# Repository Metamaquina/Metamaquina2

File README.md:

Metamaquina2
============

Metamaquina 2 - fully parametric 3D printer

Manufacturing Instructions
==========================

This is a 3d printer project that is completely designed using the parametric CAD tools
 provided by OpenSCAD. In order to deal with this source code you'll need to install OpenSCAD,
following the instructions at: www.openscad.org

The main structure of the machine is built using lasercut MDF panels. The curves for lasercutting 
can be exported to DXF by rendering the lasercutter_6mm_MDF.scad file. Open it in OpenSCAD, press F6 (to compile) and then click Design->Export DXF. The resulting DXF file can be used to cut 6mm thick MDF sheets (or you can change the thickness in the source if you plan to work with some other materials but be sure to review the 3d model in this case since some parts of the design depend on 6mm thickness).

There is also a panel for lasercutting 2mm acrylic to cover the electronics PCB and a panel for lasercutting 5mm acrylic for the ZMAX/ZMIN endstop holders and a couple of 5mm spacers for the LCExtruder. There can be generated from the lasercutter_2m_acrylic.scad and lasercutter_5m_acrylic.scad, respectively. 

The complete 3D model of the machine is described by the Metamaquina2.scad file. Open is in 
OpenSCAD and press F5 to render it.

Hacking the code
================
Feel free to send us pull requests at https://github.com/Metamaquina/Metamaquina2
 if you make any change to this design that you consider worth sharing with us.

happy hacking,

Felipe Sanches

R&D director at Metamaquina.com.br

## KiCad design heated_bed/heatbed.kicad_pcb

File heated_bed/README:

This is a heated bed design developed in KiCAD.

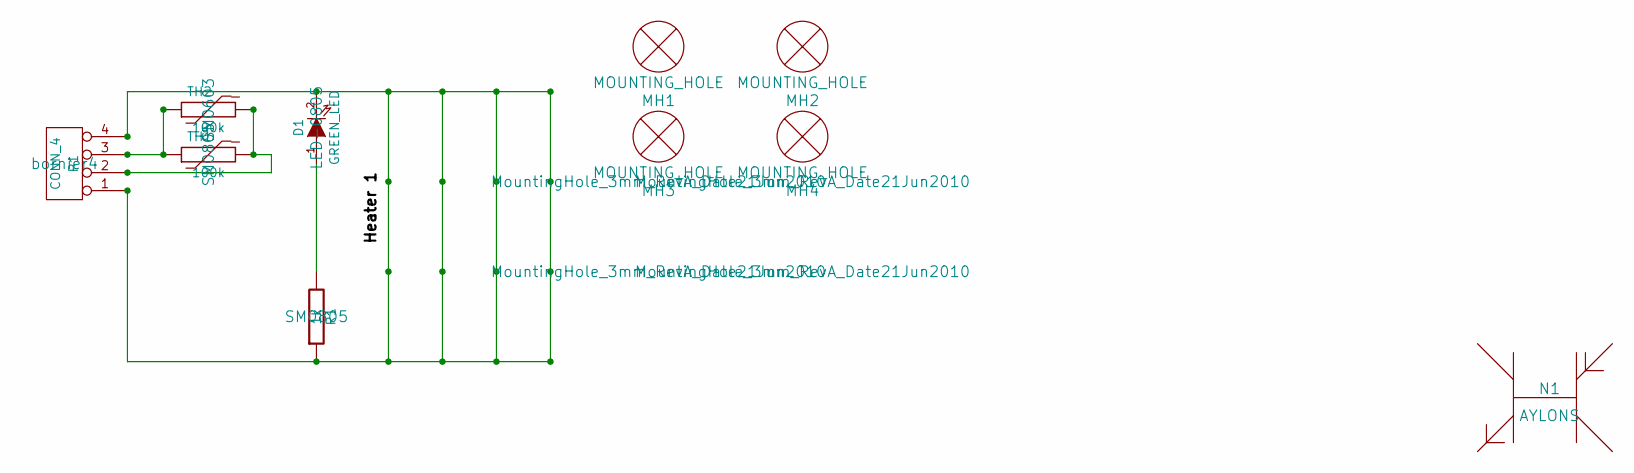
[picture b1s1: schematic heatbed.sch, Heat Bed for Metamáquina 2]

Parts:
D1: GREEN_LED; LED-0805
MH1, MH2, MH3, MH4: MOUNTING_HOLE; MountingHole_3mm_RevA_Date21Jun2010
N1: AYLONS
P1: CONN_4; bornier4
R1: 1k; SM0805
TH1: 100k; SM0805
TH2: 100k; SM0603

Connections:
unnamed: P1.3, TH1.1, TH2.1
unnamed: P1.2, TH1.2, TH2.2
unnamed: D1.1 (A), R1.2
unnamed: D1.2 (K), P1.1, P1.4, R1.1

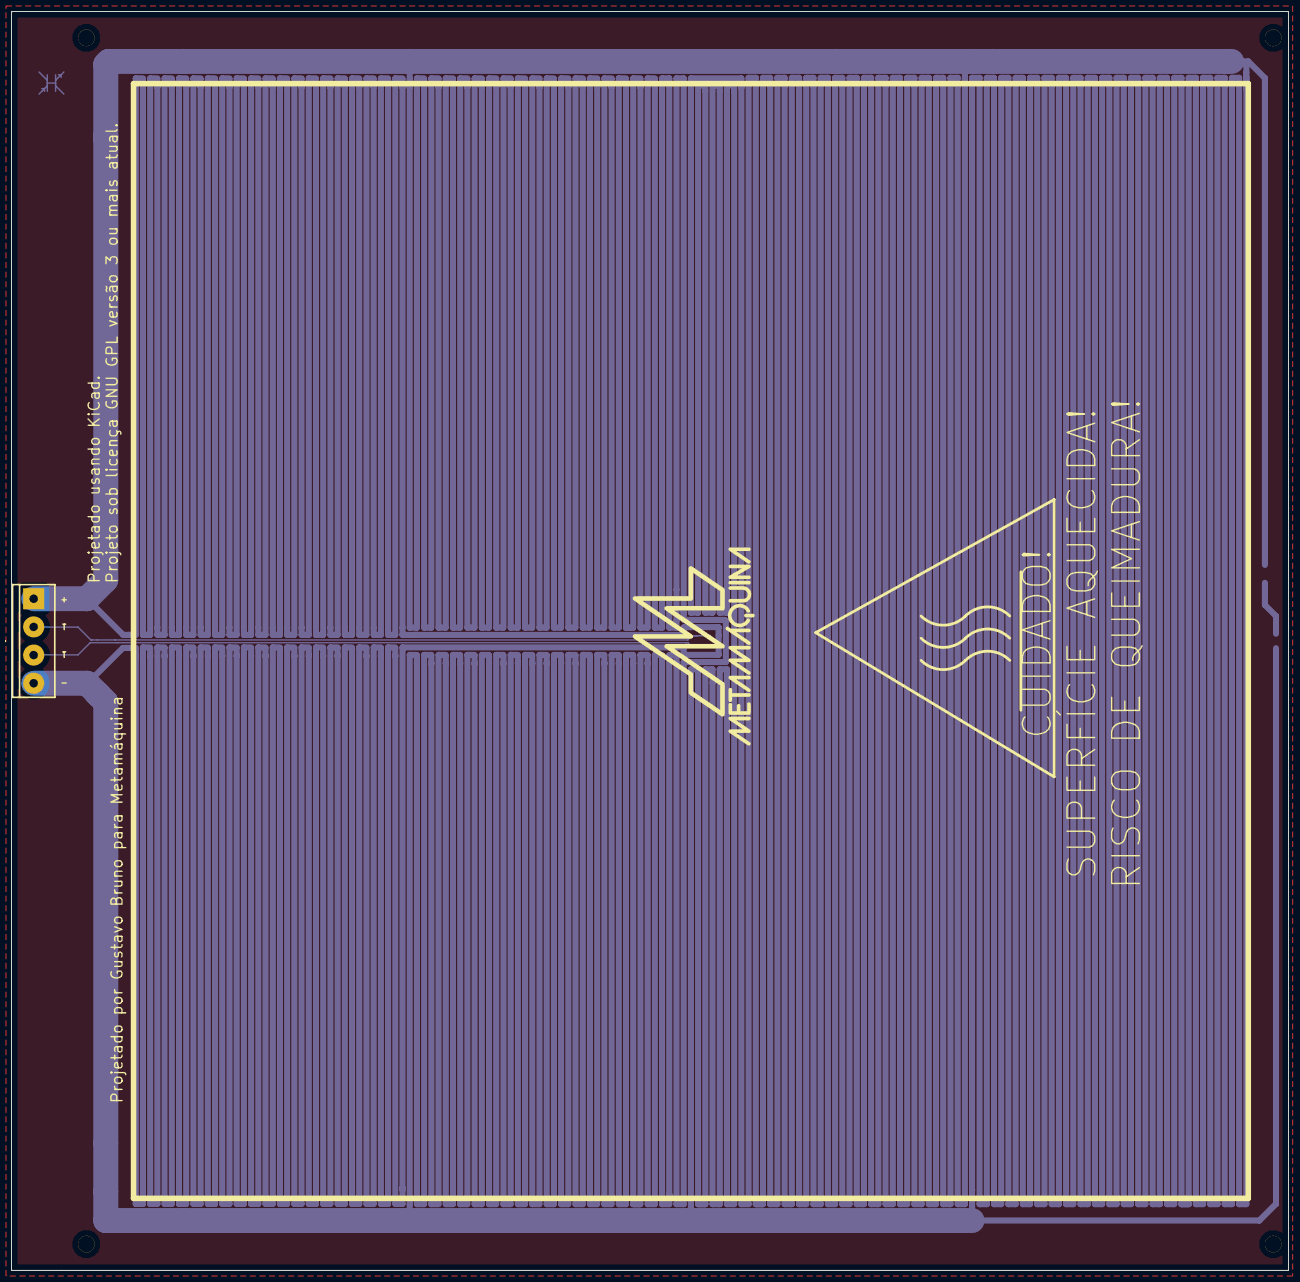
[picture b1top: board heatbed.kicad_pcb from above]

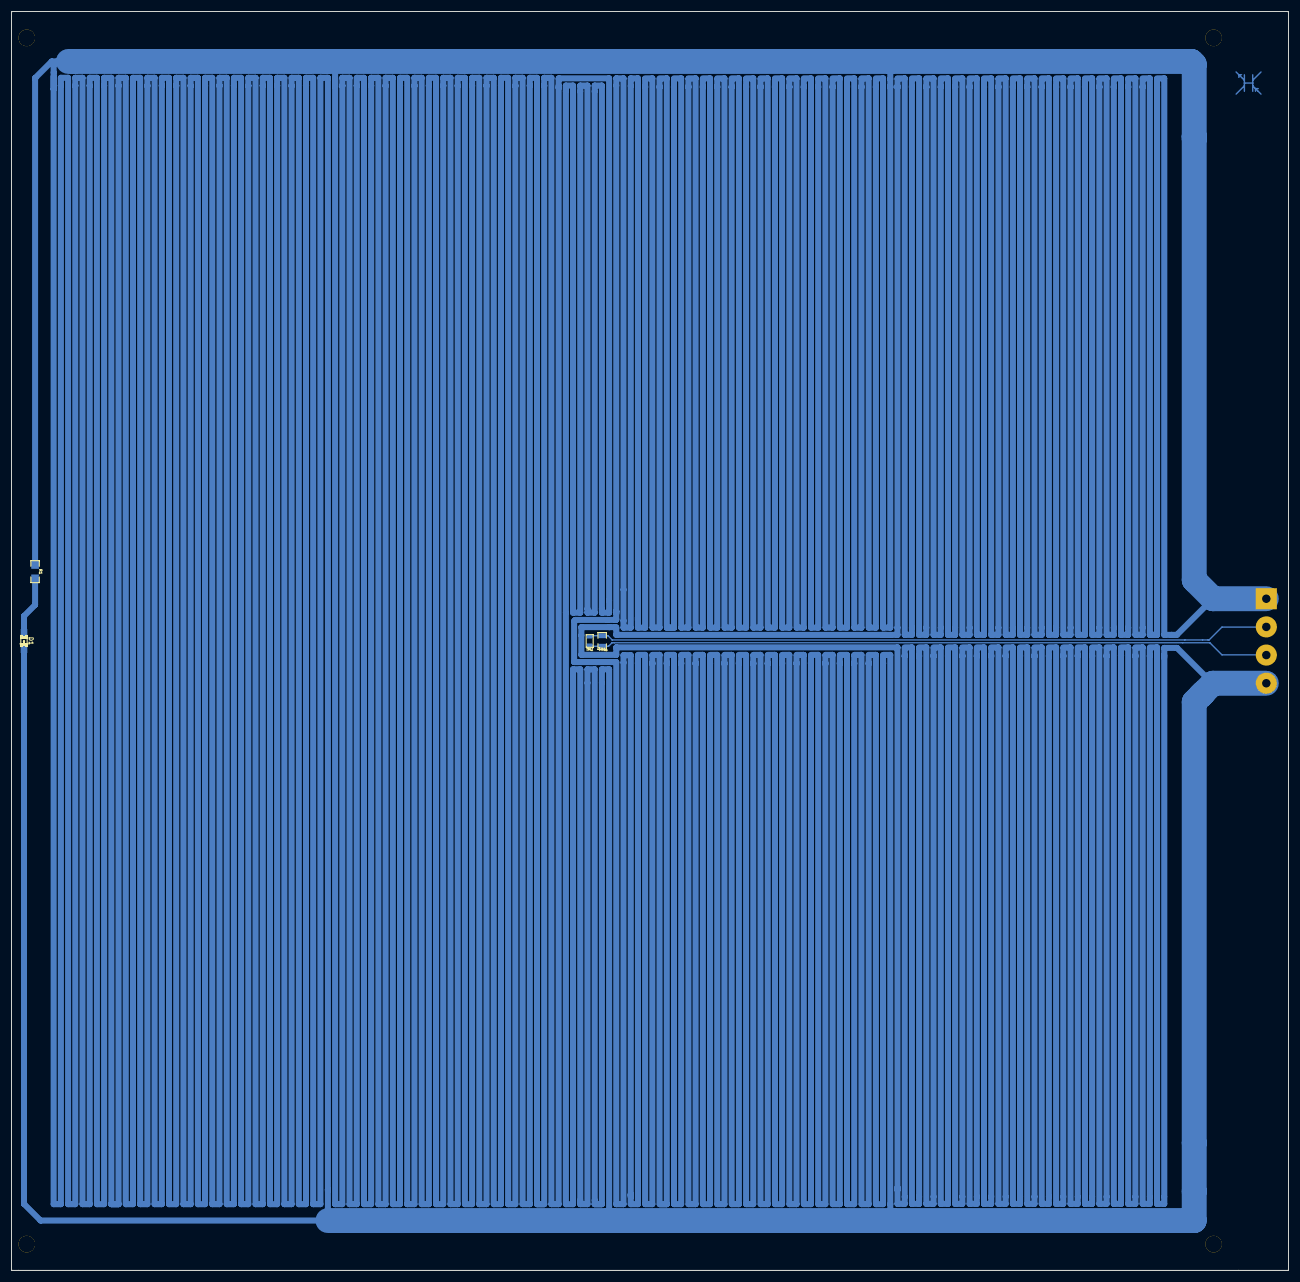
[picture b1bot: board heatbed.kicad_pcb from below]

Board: 2 copper layers, 230.2 x 227.0 mm, 10 parts (4 on the bottom side), 4 nets.

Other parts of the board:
VAL: MM_logo

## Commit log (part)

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2013-03-26 removing logo from the yplatform
2013-03-26 adding a variable that was undefined
2013-03-27 initial implementation of ZMAX endstop (W.I.P.)
2013-03-27 moving jhead and nozzle to separate scad files
2013-03-27 refactoring ZLink and modifying holes placement so that it's impossible to mount it in a wrong position.
2013-03-31 Moving the XZStage 2 centimeters closer to the front of the macihne in order to get more space for the RAMBo electronics & for the power supply.
2013-03-31 fliping positioning of the sheets for YMIN and YMAN endstops to avoid hitting the YMotor
2013-04-01 tweaking holes for wiring in the sidepanels
2013-04-01 lasercut extruder: adding cuts for filament channel and nozzle_holder
2013-04-02 Updating RAMBo power supply connector dimensions and adding bolt slots.
2013-04-04 Adding several sizes of nuts and locknuts.
2013-04-05 Adding file doc/BillOfMaterials.ods
2013-04-08 deleted: Jhn_nozzle_v4.scad
    Ja temos o nozzle.scad
2013-04-08 Updating HeatedBed and YPlatform_face dimensions.
2013-04-08 Fixing motor gear model.
2013-04-08 Adding file MM_hole.dxf.
2013-04-08 Aumentada a placa para evitar colisao com extrusor
2013-04-09 adding idler bearing to the LCextruder and implementing lasercut idler spacers
2013-04-09 improving the LC Extruder
2013-04-09 updating LCExtruder design
2013-04-09 Inserting copyright claim.
2013-04-09 fixing colors and bringing back the nozzle model rendering to the main machine model
2013-04-09 removing default "hull"-shaped hole from ZLink (keep it optional as a parameter)
2013-04-09 better placement for beltclamp mount holes in the xcarriage
2013-04-09 tweaking ZMAX endstop
2013-04-09 hull-shaped holes for YMAX/YMIN endstop wiring
2013-04-10 adding another bolt to the LCExtruder
2013-04-10 mega hole for RAMBo wiring
2013-04-10 prototipo enviado para corte em 10 de abril de 2013 (MM2_RC1)
2013-04-10 Rotating YPlatform extra length.
2013-04-17 Feitas fresas e cantos arredondados
2013-04-18 Adding 0.05 mm (epsilon/2) to Z rods M8 holes.
2013-04-18 Adding variable rods_diameter_clearance = 0.1
2013-04-19 Configuracao da geracao dos gerbers
2013-04-19 Fixing the build. There were semi-colons missing in the end of 2 statements.
2013-04-19 Fix Issue #34
2013-04-22 fix issue #37
2013-04-22 fix issue #46 : Add ZMIN/ZMAX holders to a lasercutter panel
2013-04-23 Enlarging hole for extruder wires.
2013-04-23 fix mount holes for ZMIN/ZMAX endstops
2013-04-24 refactoring material colors and selective rendering
2013-04-24 Updating references to extruder gears.
2013-04-25 Correcoes apos prototipo fresado:
    Bug que colava duas trilhas
    Led avancado
    Linha de distribuicao mais proxima
    Textos do silk realinhados
    Remoca do desenho de quente
    Nome da placa
2013-04-25 conditionally render LCExtruder
2013-04-25 wip: improving placement of cable clips. Still got to finish this...
2013-04-26 Inverting small gear (better for printing).
2013-04-26 Removing right panel and bottom panel ziptie holes (not needed anymore).
2013-04-26 updating the heated bed outline for lasercutting
    Also adding an utils.scad file with a module that will help me make cuts in the edges of lasercut sheets.
2013-04-26 Adding connector details to the NEMA17 model and rotating the motors to serve as machine build documentation
2013-04-26 fix issue #58 : make sure every motor has a ziptie for holding its wires in place
2013-04-26 fix issue #54 : Adding in sidepanel hole for XMotor wire
2013-04-27 Updating coupling model and adding 2 bolt holes.
2013-04-27 adding file that was missing in a previous commit: heated_bed.scad
2013-04-27 moving render configs and color declarations to header files
2013-04-29 A detailed version of a 608zz bearing 3d model (just for fun :-D) Inspired by "PRECISION MODELLING - A guide to modelling parts and components accurately using Blender" by Robert Burke
2013-04-29 wip: issue #51 (YMIN/YMAX spacers)
2013-04-29 fix YCarPosition coordinate calculation and comment out XYZ CarPosition animation routines.
2013-04-29 Fix issue #59 : One single panel with everything that needs to be lasercut for manufacturing one 3d printer
2013-04-30 fix issue #55 : enlarge beltclamps so that they are stronger when lasercut
2013-04-30 Making sure the nut_gap in the lasercut extruder is large enough for an M3 nut. And further refactoring nuts and washers.
2013-05-01 add a parameter to optionally remove the frontal portion of the XPlatform to increase visibility of the 3d model being printed
2013-05-02 offseting slightly the ziptie holes for the extruder motor so that they are not so close to the LM8UU bearings underneath the XCarriage bottom sheet.
2013-05-02 fix issue #65 : Mirror ZMIN lasercut outlines
2013-05-02 adding a helper trapezoid drawing function
2013-05-02 fix issue #63 : updating cable clip sizes
2013-05-03 refactoring nozzle tip distance math
2013-05-03 fix heated bed / build platform z coordinates calculation
2013-05-03 fix: extra zmin area in the sidepanel was obstructing part of the bottompanel slot
2013-05-03 add top wiring hole parts to the lasercutter panel
2013-05-03 corte encomendado da MM2_RC2
2013-05-12 making xcarriage design a bit more parametric
2013-05-13 Drafting Bill of materials automation
2013-05-13 w.i.p.: BillOfMaterials
2013-05-14 w.i.p. BillOfMaterials
2013-05-14 refactoring spacers to a dedicated SCAD file and updating BillOfMaterials
2013-05-15 refactoring spacers model
2013-05-15 cleanup: removing deprecated Printrbot extruder files
2013-05-15 updating copyright headers
2013-05-16 minor tweak in BOM output formatting style
2013-05-20 refactoring power supply code
2013-05-21 implementing a box for hiding the PowerSuply wires
2013-05-21 updating cable clip sizes for lower wiring
2013-05-21 fix size of the hole for passing the zmax microswitch
2013-05-21 change ABS color to black
2013-05-21 tweak positioning of wire channel in the endstop spacers
2013-05-21 increase the power supply box size a bit
2013-05-21 wip PSU box
2013-05-22 fixo positioning of a tslot shape in the power supply box
2013-05-22 enlarging holes in xcarriage sandwich face so that we have screwdriver access to the extruder mount bolts
2013-05-22 defining the radius of the hole in the TopPanel for the extruder wiring
2013-05-22 refactoring lasercut endstop holders
2013-05-23 improving calibration hints
2013-05-23 material() markup and better rendering controls
2013-05-23 update wiring schematics
2013-05-26 fix calculation of calibration measures (to consider tslot holes' clearance)
2013-05-27 symmetry: both sidepanels have an extra-area for the zmin (even if only the left one is used for holding the zmin endstop)
2013-05-27 remiving oblong holes from the lcextruder handle (using simple round M4 holes, instead)
2013-05-27 adding beltclamps for the y belt to the CAD model and to the lasercutter panel
2013-05-31 adding a parameter to define the radius of the cut in extruder idler side faces for attaching the smooth rod
2013-06-03 adding bolts and washers to the XCarriage belt clamps
2013-06-03 minor tweaks
2013-06-03 Adicionando cabeçalho ao diagrama
2013-06-04 using M3 bolts and spacers to hit YMIN/YMAX endstops
2013-06-04 adding two extra endstop spacers (for YMIN/YMAX) to the laser cutter plate
2013-06-07 initial implementation of a filament spool holder design
2013-06-07 widening the hole for the X belt in the XEnds
2013-06-07 symmetry in the power supply bottom face
2013-06-07 fixing BOM item (extruder idler: "threaded rod" => "smooth rod")
2013-06-07 m3 diameter
2013-06-12 Wiring enviado para o fabricante
2013-06-13 dimensionamento de acordo com o tamanho do rolo
2013-06-13 mirroring faces in the laser cutter panel for aestethical purposes regarding the burnt side
2013-06-14 minor refactoring
2013-06-14 clearance in the PSU-box front and back faces to deal with variations in the dimentions of parts supplied by the PSU manufacturer
2013-06-14 removing LCExtruder spacers from the main laser panel. These spacers are now cut in 5mm acrylic
2013-06-14 lcextruder is made of 5mm acrylic
2013-06-14 adding a screw access hole for easier xcarriage maintainence
2013-06-14 changing mount position of the small y_bearing_sandwich to reduce the risk of getting the heated bed wiring stuck in it
2013-06-14 repositioning PSU parts in the lasercutter plate
2013-06-14 2mm acrylic lasercutter panel (electronics cover sheet)
2013-06-14 removing unnecessary endstop holders from the MDF lasercutter panel and adding a 5mm acrylic lasercutter panel for those nd for the 2 extruder idler spacers
2013-06-14 renaming laser cutter panel
2013-06-14 adding a label to the RA6 mount place to avoid mistakes during manufacturing
2013-06-14 fixing calibration math
2013-06-19 logo and tslot inclusion
2013-06-19 bolt hole added
2013-06-26 refactoring
2013-06-26 top_cut adjust
2013-06-28 rotate the panel with M logo
2013-06-28 wiring diagram revC
2013-07-01 calibration rules
2013-07-02 Fixing typos
2013-07-02 finish the calibration rules - the file that ends in -conf shows the rules in the 3D printer, without it shows only the front and rear rules
2013-07-02 Fix rods and bars size printed in BOM
2013-07-02 Modified BillOfMaterials calls to include part ref. Fixed belt modules naming and belt BOM calls Fix rods and bars size printed in BOM Fixed a few typos and parts naming
    modified: 608zz_bearing.scad
    modified: Metamaquina2.scad
    modified: NEMA.scad
    modified: PowerSupply.scad
    modified: RAMBo.scad
    modified: ZLink.scad
2013-07-04 inclusion of nuts and bolts and retired a don't functional part of the code
2013-07-09 Idler must have 2 acrylic 5mm spacers to accomodate laser cut error
2013-07-10 Replacing 38mm hexspacer with 32mm hexspacer
2013-07-16 mirroring the LC Extruder
2013-07-16 canonical positioning of axes
2013-07-25 fix issue #93: Enlarge the top wiring hole diameter
    https://github.com/Metamaquina/Metamaquina2/issues/93
2013-07-25 fix issue #95 : placement of zipties for the endstop wires
2013-07-26 trying to fix issue #90 :Profundidade do sulco para encaixe do dissipador de PEEK
2013-07-29 improve nuts/lock-nuts implementation
2013-07-29 removing unused zip-tie holes for the RAMBo wiring
2013-07-29 tweak the shape of the sidepanel so that the power supply is fully contained in the rightpanel area
2013-07-29 adding a new type of metamaquina 3d printer including 2 extruders
2013-07-29 tweak laser cutter panel to avoid collisions
2013-07-29 adding new parts to the laser cutter panel
2013-07-31 centering the power supply on/off switch
2013-07-31 new realistic peep draw
2013-08-01 fix issue #100 tslot holes for width=0 should be simply a single M3 hole
2013-08-05 tweaking positioning of the safety ZMIN endstop
2013-08-05 revC batch_run
2013-08-06 changing the format of the extruder
2013-08-06 exclusion of a rubber cilinder outside the J head
2013-08-06 Including the Filament Spool Holder
2013-08-06 removing explicit rounding $fn=20 from RAMBo holes
2013-08-09 New Metamaquina with 2 extruders
2013-08-14 Including the carriage in the panels
2013-08-23 adding the new extruder with B tube
2013-08-26 retired unnecessaries spaces
2013-08-26 New power supply naming
2013-08-29 New top wiring hole aux modules; larger hole
2013-08-30 Minor BOM adjustments
2013-09-10 larger base radius for the small extruder gear
2013-09-11 flipping the small extruder gear upside down
2013-09-11 fixing grubscrew hole in the small extruder gear
2013-09-12 adding a parametric thickness for the side wings of the ZLink
2013-09-17 thicker/stronger wings for the ZLink
2013-10-03 exclusion of some holes to the rules
2013-10-15 new ZLink design: harder, better, (faster ?!) stronger
2013-10-30 realoading this branch
2013-10-31 New files extruders-clamp for our peek extruders-clamp-1 for seemecnc
2013-12-22 again
2018-01-24 Revert "final review of the original Metamaquina2 files"
    This reverts commit 7661948f7e02bf8e7102829764f8881f861681e3.
2018-01-24 Revert "creating branch"
    This reverts commit cb69a04c0ebcff373e8821dceec0a140e0080905.

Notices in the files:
heated_bed/heatbed.kicad_pcb:
Projeto sob licença GNU GPL versão 3 ou mais atual.
heated_bed/heatbed.sch:
Licensed under GNU GPLv3 (or later)
